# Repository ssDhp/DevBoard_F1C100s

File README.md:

# DevBoard_F1C100s Rev 1
F1C100s based embedded Linux development board

## Schematic

## Layout
2 Layers 75x50 mm  

## Render

## Assembled PCB

## Note
- Board enumerates over USB but randomly resets likely due to missing bulk capacitor on VBUS.
- Other issues:
    - Wrong voltage on UVCC pin of F1C100s
    - Missing pull-up on CS pin of Flash

# DevBoard_F1C100s Rev2

## Schematic

## Layout
4 Layers 60x45mm

## Render

## Note
 - **TODO:** Assemble and Test rev 2 of the dev board.

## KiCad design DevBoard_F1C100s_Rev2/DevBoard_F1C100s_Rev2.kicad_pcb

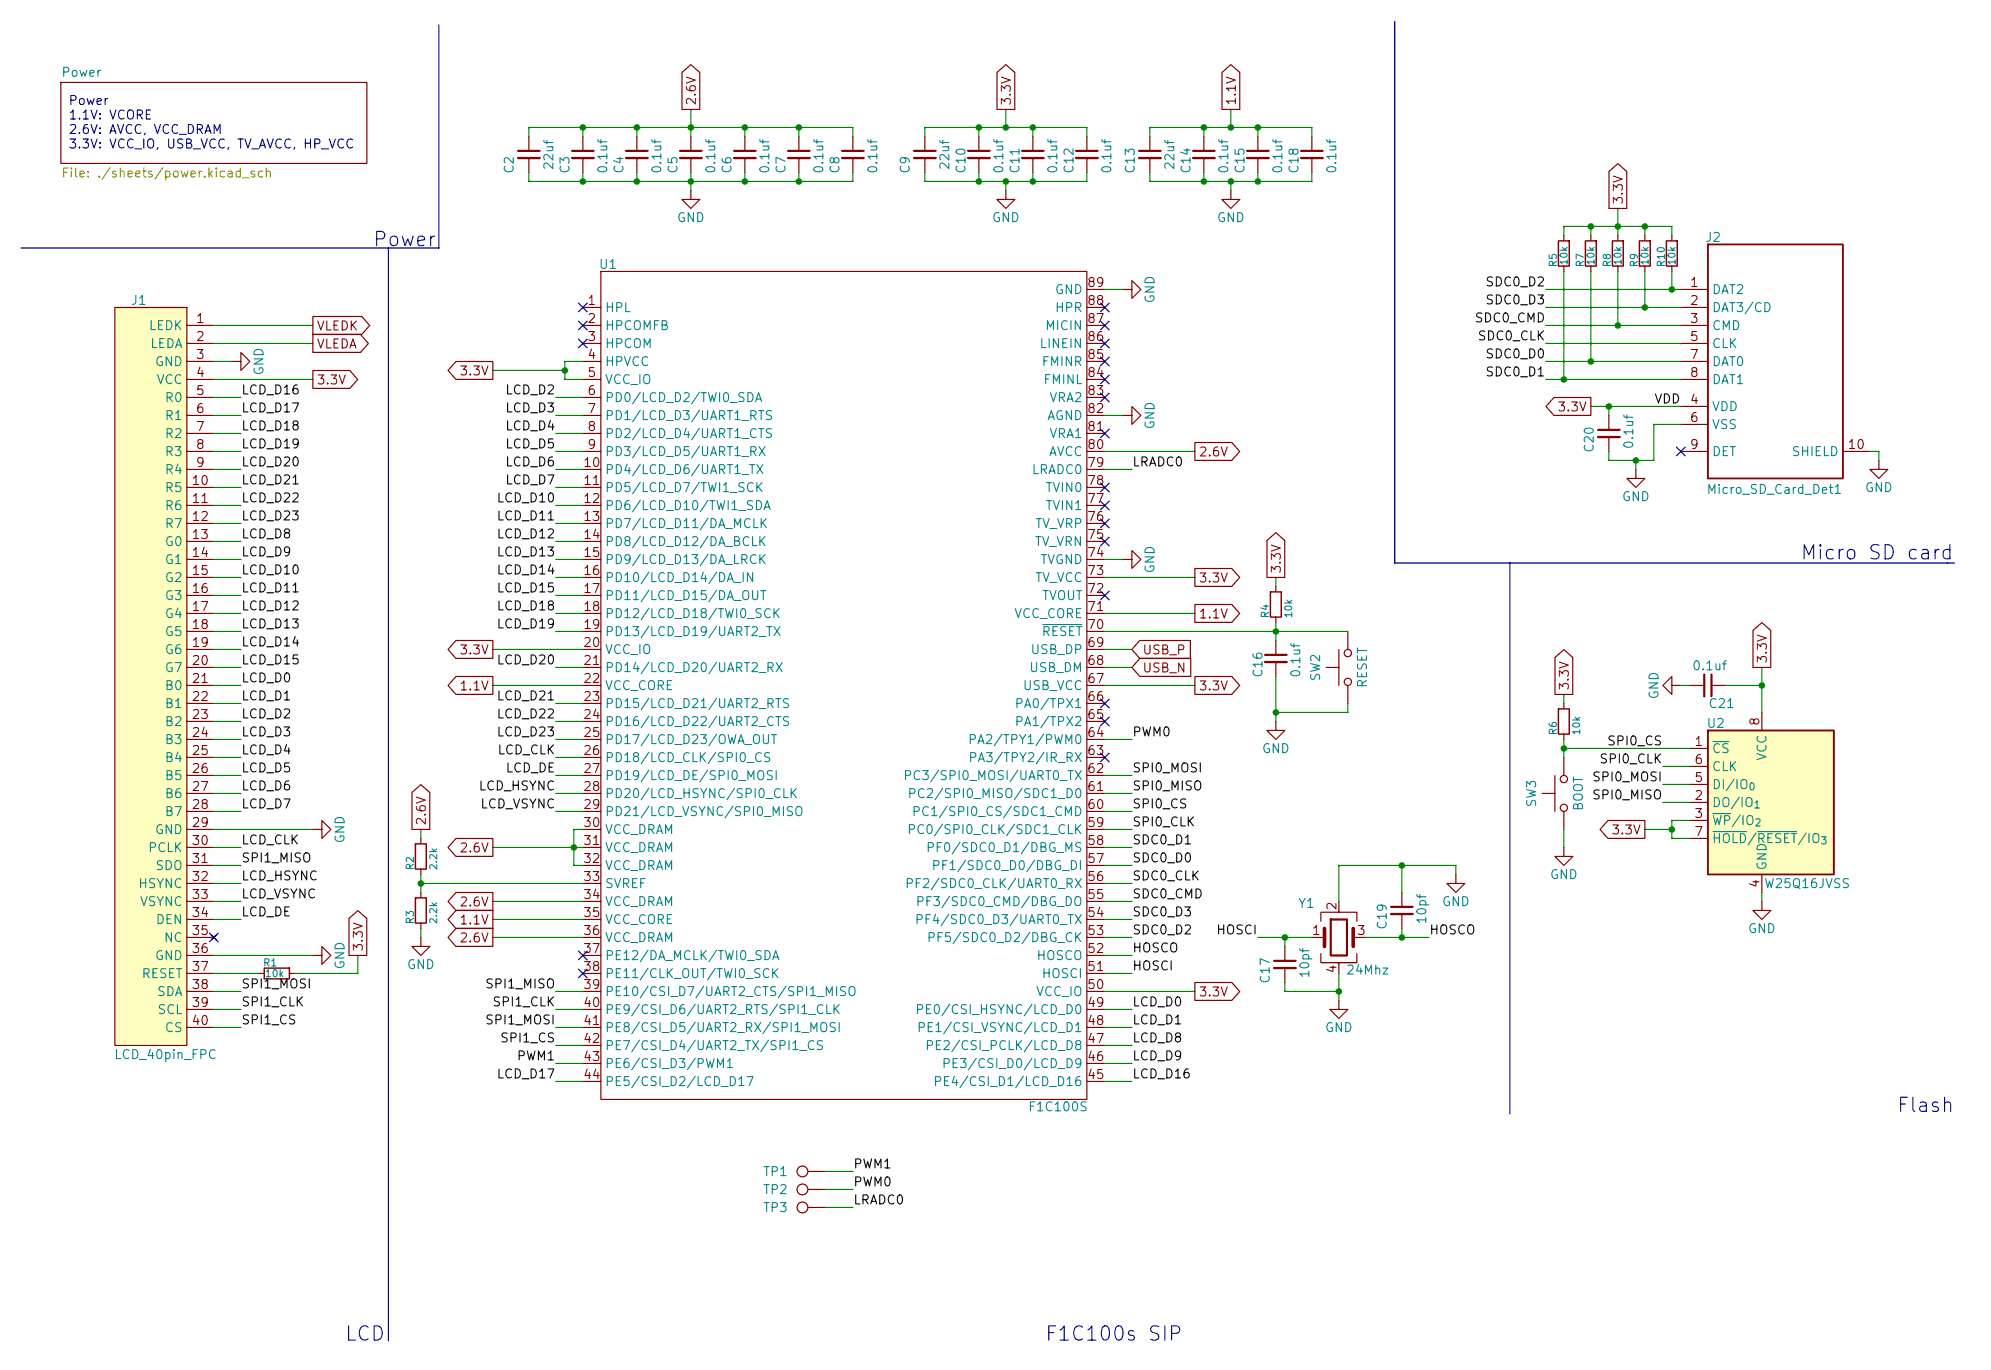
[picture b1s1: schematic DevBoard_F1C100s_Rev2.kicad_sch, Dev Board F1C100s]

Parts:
C2, C9, C13: 22uf; C_0603_1608Metric_Pad1.08x0.95mm_HandSolder
C3, C4, C5, C6, C7, C8, C10, C11, C12, C14, C15, C16, C18, C20, C21: 0.1uf; C_0603_1608Metric_Pad1.08x0.95mm_HandSolder
C17, C19: 10pf; C_0603_1608Metric_Pad1.08x0.95mm_HandSolder
J1: LCD_40pin_FPC; 40pin_0.5mm_Vertical
J2: Micro_SD_Card_Det1; sd_card_10p
R1, R4, R5, R6, R7, R8, R9, R10: 10k; R_0603_1608Metric_Pad0.98x0.95mm_HandSolder
R2, R3: 2.2k; R_0603_1608Metric_Pad0.98x0.95mm_HandSolder
SW2: RESET; SW_SPST_CK_RS282G05A3
SW3: BOOT; SW_SPST_CK_RS282G05A3
TP1, TP2, TP3: TestPoint; TestPoint_Pad_D1.0mm
U1: F1C100S; QFN-88_EP_10x10_Pitch0.4mm
U2: W25Q16JVSS; SOIC-8_5.3x5.3mm_P1.27mm
Y1: 24Mhz; Crystal_SMD_3225-4Pin_3.2x2.5mm_HandSoldering

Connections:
1.1V: C13.1, C14.1, C15.1, C18.1, U1.22 (VCC_CORE), U1.35 (VCC_CORE), U1.71 (VCC_CORE); also elsewhere on the board
2.6V: C2.1, C3.1, C4.1, C5.1, C6.1, C7.1, C8.1, R2.1, U1.30 (VCC_DRAM), U1.31 (VCC_DRAM), U1.32 (VCC_DRAM), U1.34 (VCC_DRAM), U1.36 (VCC_DRAM), U1.80 (AVCC); also elsewhere on the board
3.3V: C9.1, C10.1, C11.1, C12.1, C20.1, C21.1, J1.4 (VCC), J2.4 (VDD), R1.1, R4.1, R5.1, R6.1, R7.1, R8.1, R9.1, R10.1, U1.4 (HPVCC), U1.5 (VCC_IO), U1.20 (VCC_IO), U1.50 (VCC_IO), U1.67 (USB_VCC), U1.73 (TV_VCC), U2.3 (~WP/IO_{2}), U2.7 (~HOLD/~RESET/IO_{3}), U2.8 (VCC); also elsewhere on the board
/HOSCI: C17.1, U1.51 (HOSCI), Y1.1
/HOSCO: C19.2, U1.52 (HOSCO), Y1.3
/LCD_CLK: J1.30 (PCLK), U1.26 (PD18/LCD_CLK/SPI0_CS)
/LCD_D0: J1.21 (B0), U1.49 (PE0/CSI_HSYNC/LCD_D0)
/LCD_D1: J1.22 (B1), U1.48 (PE1/CSI_VSYNC/LCD_D1)
/LCD_D2: J1.23 (B2), U1.6 (PD0/LCD_D2/TWI0_SDA)
/LCD_D3: J1.24 (B3), U1.7 (PD1/LCD_D3/UART1_RTS)
/LCD_D4: J1.25 (B4), U1.8 (PD2/LCD_D4/UART1_CTS)
/LCD_D5: J1.26 (B5), U1.9 (PD3/LCD_D5/UART1_RX)
/LCD_D6: J1.27 (B6), U1.10 (PD4/LCD_D6/UART1_TX)
/LCD_D7: J1.28 (B7), U1.11 (PD5/LCD_D7/TWI1_SCK)
/LCD_D8: J1.13 (G0), U1.47 (PE2/CSI_PCLK/LCD_D8)
/LCD_D9: J1.14 (G1), U1.46 (PE3/CSI_D0/LCD_D9)
/LCD_D10: J1.15 (G2), U1.12 (PD6/LCD_D10/TWI1_SDA)
/LCD_D11: J1.16 (G3), U1.13 (PD7/LCD_D11/DA_MCLK)
/LCD_D12: J1.17 (G4), U1.14 (PD8/LCD_D12/DA_BCLK)
/LCD_D13: J1.18 (G5), U1.15 (PD9/LCD_D13/DA_LRCK)
/LCD_D14: J1.19 (G6), U1.16 (PD10/LCD_D14/DA_IN)
/LCD_D15: J1.20 (G7), U1.17 (PD11/LCD_D15/DA_OUT)
/LCD_D16: J1.5 (R0), U1.45 (PE4/CSI_D1/LCD_D16)
/LCD_D17: J1.6 (R1), U1.44 (PE5/CSI_D2/LCD_D17)
/LCD_D18: J1.7 (R2), U1.18 (PD12/LCD_D18/TWI0_SCK)
/LCD_D19: J1.8 (R3), U1.19 (PD13/LCD_D19/UART2_TX)
/LCD_D20: J1.9 (R4), U1.21 (PD14/LCD_D20/UART2_RX)
/LCD_D21: J1.10 (R5), U1.23 (PD15/LCD_D21/UART2_RTS)
/LCD_D22: J1.11 (R6), U1.24 (PD16/LCD_D22/UART2_CTS)
/LCD_D23: J1.12 (R7), U1.25 (PD17/LCD_D23/OWA_OUT)
/LCD_DE: J1.34 (DEN), U1.27 (PD19/LCD_DE/SPI0_MOSI)
/LCD_HSYNC: J1.32 (HSYNC), U1.28 (PD20/LCD_HSYNC/SPI0_CLK)
/LCD_VSYNC: J1.33 (VSYNC), U1.29 (PD21/LCD_VSYNC/SPI0_MISO)
/LRADC0: TP3.1, U1.79 (LRADC0)
/PWM0: TP2.1, U1.64 (PA2/TPY1/PWM0)
/PWM1: TP1.1, U1.43 (PE6/CSI_D3/PWM1)
/SDC0_CLK: J2.5 (CLK), U1.56 (PF2/SDC0_CLK/UART0_RX)
/SDC0_CMD: J2.3 (CMD), R8.2, U1.55 (PF3/SDC0_CMD/DBG_DO)
/SDC0_D0: J2.7 (DAT0), R7.2, U1.57 (PF1/SDC0_D0/DBG_DI)
/SDC0_D1: J2.8 (DAT1), R5.2, U1.58 (PF0/SDC0_D1/DBG_MS)
/SDC0_D2: J2.1 (DAT2), R10.2, U1.53 (PF5/SDC0_D2/DBG_CK)
/SDC0_D3: J2.2 (DAT3/CD), R9.2, U1.54 (PF4/SDC0_D3/UART0_TX)
/SPI0_CLK: U1.59 (PC0/SPI0_CLK/SDC1_CLK), U2.6 (CLK)
/SPI0_CS: R6.2, SW3.2, U1.60 (PC1/SPI0_CS/SDC1_CMD), U2.1 (~CS)
/SPI0_MISO: U1.61 (PC2/SPI0_MISO/SDC1_D0), U2.2 (DO/IO_{1})
/SPI0_MOSI: U1.62 (PC3/SPI0_MOSI/UART0_TX), U2.5 (DI/IO_{0})
/SPI1_CLK: J1.39 (SCL), U1.40 (PE9/CSI_D6/UART2_RTS/SPI1_CLK)
/SPI1_CS: J1.40 (CS), U1.42 (PE7/CSI_D4/UART2_TX/SPI1_CS)
/SPI1_MISO: J1.31 (SDO), U1.39 (PE10/CSI_D7/UART2_CTS/SPI1_MISO)
/SPI1_MOSI: J1.38 (SDA), U1.41 (PE8/CSI_D5/UART2_RX/SPI1_MOSI)
GND: C2.2, C3.2, C4.2, C5.2, C6.2, C7.2, C8.2, C9.2, C10.2, C11.2, C12.2, C13.2, C14.2, C15.2, C16.2, C17.2, C18.2, C19.1, C20.2, C21.2, J1.3 (GND), J1.29 (GND), J1.36 (GND), J2.6 (VSS), J2.10 (SHIELD), R3.2, SW2.1, SW3.1, U1.74 (TVGND), U1.82 (AGND), U1.89 (GND), U2.4 (GND), Y1.2, Y1.4; also elsewhere on the board
unnamed: J1.37 (RESET), R1.2
unnamed: R2.2, R3.1, U1.33 (SVREF)
unnamed: C16.1, R4.2, SW2.2, U1.70 (~RESET)
USB_N: U1.68 (USB_DM); also elsewhere on the board
USB_P: U1.69 (USB_DP); also elsewhere on the board
VLEDA: J1.2 (LEDA); also elsewhere on the board
VLEDK: J1.1 (LEDK); also elsewhere on the board

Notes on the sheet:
Micro SD card
LCD
Power
Flash
F1C100s SIP
Power 1.1V: VCORE 2.6V: AVCC, VCC_DRAM 3.3V: VCC_IO, USB_VCC, TV_AVCC, HP_VCC

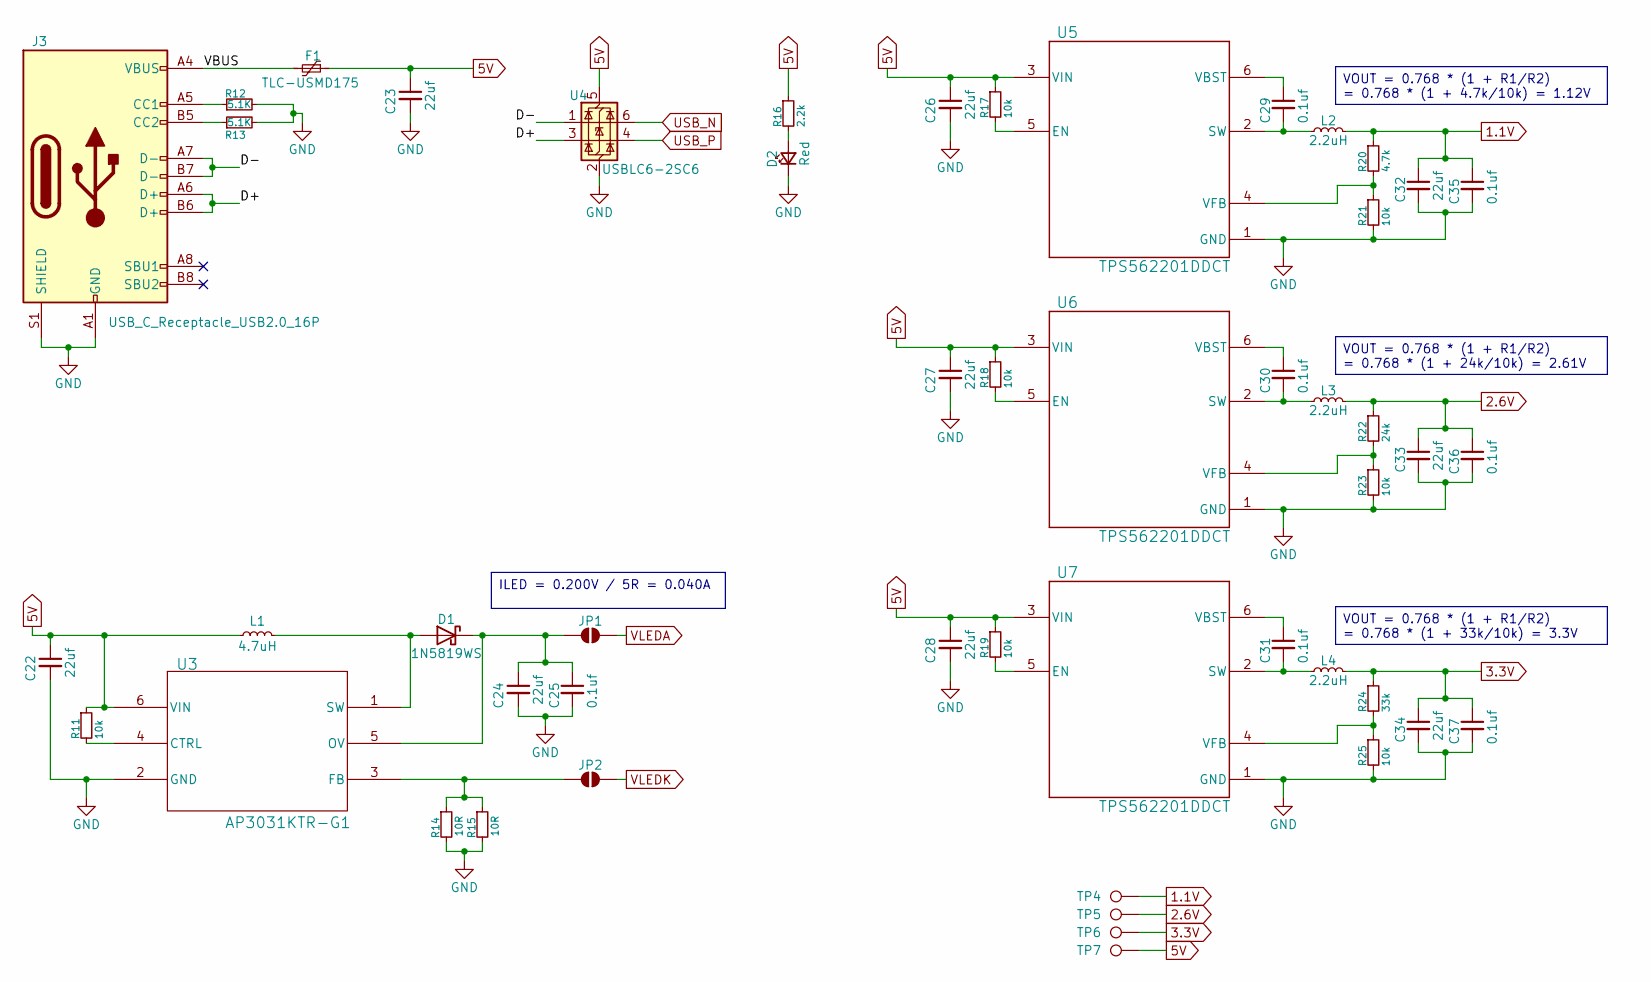
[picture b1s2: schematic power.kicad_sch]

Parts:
C22, C23, C24, C26, C27, C28, C32, C33, C34: 22uf; C_0603_1608Metric_Pad1.08x0.95mm_HandSolder
C25, C29, C30, C31, C35, C36, C37: 0.1uf; C_0603_1608Metric_Pad1.08x0.95mm_HandSolder
D1: 1N5819WS; D_SOD-523
D2: Red; LED_0603_1608Metric_Pad1.05x0.95mm_HandSolder
F1: TLC-USMD175; Fuse_1210_3225Metric_Pad1.42x2.65mm_HandSolder
J3: USB_C_Receptacle_USB2.0_16P; USB_C_Receptacle_HRO_TYPE-C-31-M-12
JP1, JP2: SolderJumper_2_Open; SolderJumper-2_P1.3mm_Open_Pad1.0x1.5mm
L1: 4.7uH; L_0805_2012Metric_Pad1.15x1.40mm_HandSolder
L2, L3, L4: 2.2uH; L_Sunlord_SWPA4030S
R11, R17, R18, R19, R21, R23, R25: 10k; R_0603_1608Metric_Pad0.98x0.95mm_HandSolder
R12, R13: 5.1K; R_0603_1608Metric_Pad0.98x0.95mm_HandSolder
R14, R15: 10R; R_0603_1608Metric_Pad0.98x0.95mm_HandSolder
R16: 2.2k; R_0603_1608Metric_Pad0.98x0.95mm_HandSolder
R20: 4.7k; R_0603_1608Metric_Pad0.98x0.95mm_HandSolder
R22: 24k; R_0603_1608Metric_Pad0.98x0.95mm_HandSolder
R24: 33k; R_0603_1608Metric_Pad0.98x0.95mm_HandSolder
TP4, TP5, TP6, TP7: TestPoint; TestPoint_Pad_D1.0mm
U3: AP3031KTR-G1; SOT23-6_DIO
U4: USBLC6-2SC6; SOT-23-6
U5, U6, U7: TPS562201DDCT; DDC0006A_N

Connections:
1.1V: C32.1, C35.1, L2.2, R20.1, TP4.1; also elsewhere on the board
2.6V: C33.1, C36.1, L3.2, R22.1, TP5.1; also elsewhere on the board
3.3V: C34.1, C37.1, L4.2, R24.1, TP6.1; also elsewhere on the board
5V: C22.1, C23.1, C26.1, C27.1, C28.1, F1.1, L1.1, R11.1, R16.1, R17.1, R18.1, R19.1, TP7.1, U3.6 (VIN), U4.5 (VBUS), U5.3 (VIN), U6.3 (VIN), U7.3 (VIN)
/Power/D+: J3.A6 (D+), J3.B6 (D+), U4.3 (I/O2)
/Power/D-: J3.A7 (D-), J3.B7 (D-), U4.1 (I/O1)
/Power/VBUS: F1.2, J3.A4 (VBUS), J3.A9 (VBUS), J3.B4 (VBUS), J3.B9 (VBUS)
GND: C22.2, C23.2, C24.2, C25.2, C26.2, C27.2, C28.2, C32.2, C33.2, C34.2, C35.2, C36.2, C37.2, D2.1 (K), J3.A1 (GND), J3.A12 (GND), J3.B1 (GND), J3.B12 (GND), J3.S1 (SHIELD), R12.2, R13.2, R14.2, R15.2, R21.2, R23.2, R25.2, U3.2 (GND), U4.2 (GND), U5.1 (GND), U6.1 (GND), U7.1 (GND); also elsewhere on the board
unnamed: D1.2 (A), L1.2, U3.1 (SW)
unnamed: C24.1, C25.1, D1.1 (K), JP1.1 (A), U3.5 (OV)
unnamed: D2.2 (A), R16.2
unnamed: J3.A5 (CC1), R12.1
unnamed: J3.B5 (CC2), R13.1
unnamed: JP2.1 (A), R14.1, R15.1, U3.3 (FB)
unnamed: R11.2, U3.4 (CTRL)
unnamed: R17.2, U5.5 (EN)
unnamed: C29.2, L2.1, U5.2 (SW)
unnamed: C29.1, U5.6 (VBST)
unnamed: R20.2, R21.1, U5.4 (VFB)
unnamed: R18.2, U6.5 (EN)
unnamed: C30.2, L3.1, U6.2 (SW)
unnamed: C30.1, U6.6 (VBST)
unnamed: R22.2, R23.1, U6.4 (VFB)
unnamed: R19.2, U7.5 (EN)
unnamed: C31.2, L4.1, U7.2 (SW)
unnamed: C31.1, U7.6 (VBST)
unnamed: R24.2, R25.1, U7.4 (VFB)
USB_N: U4.6 (I/O1); also elsewhere on the board
USB_P: U4.4 (I/O2); also elsewhere on the board
VLEDA: JP1.2 (B); also elsewhere on the board
VLEDK: JP2.2 (B); also elsewhere on the board

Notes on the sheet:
ILED = 0.200V / 5R = 0.040A
VOUT = 0.768 * (1 + R1/R2) = 0.768 * (1 + 4.7k/10k) = 1.12V
VOUT = 0.768 * (1 + R1/R2) = 0.768 * (1 + 24k/10k) = 2.61V
VOUT = 0.768 * (1 + R1/R2) = 0.768 * (1 + 33k/10k) = 3.3V

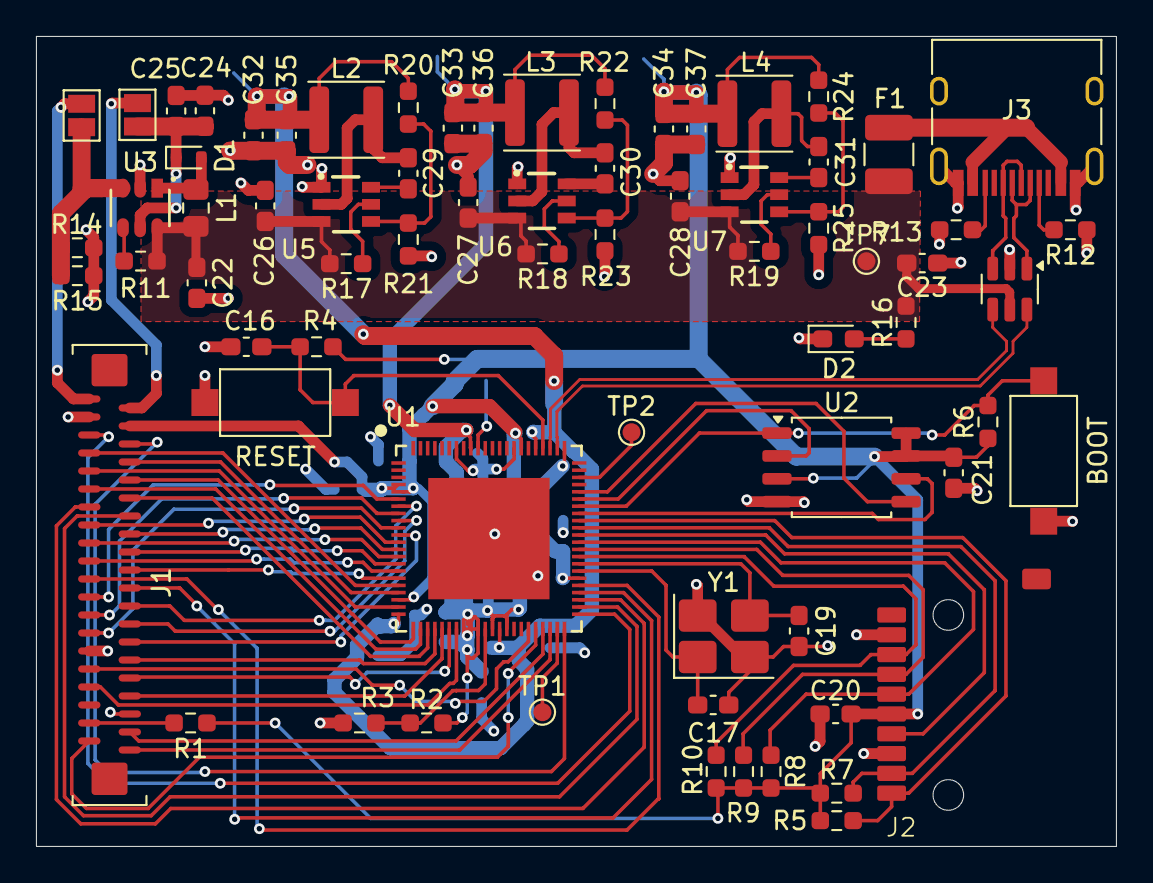
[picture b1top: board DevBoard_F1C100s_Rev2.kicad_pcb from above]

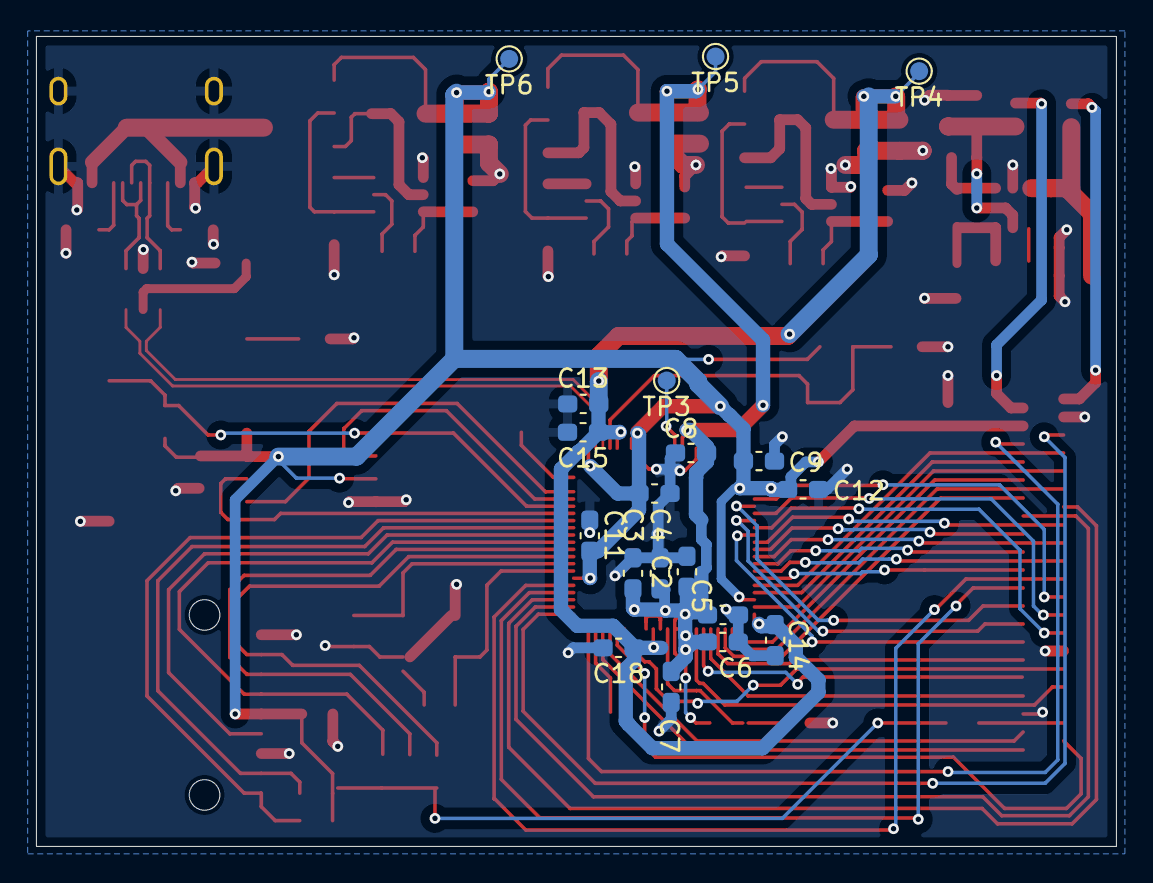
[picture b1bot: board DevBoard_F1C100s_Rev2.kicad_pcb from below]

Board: 4 copper layers, 60.0 x 45.0 mm, 90 parts (19 on the bottom side), 81 nets.

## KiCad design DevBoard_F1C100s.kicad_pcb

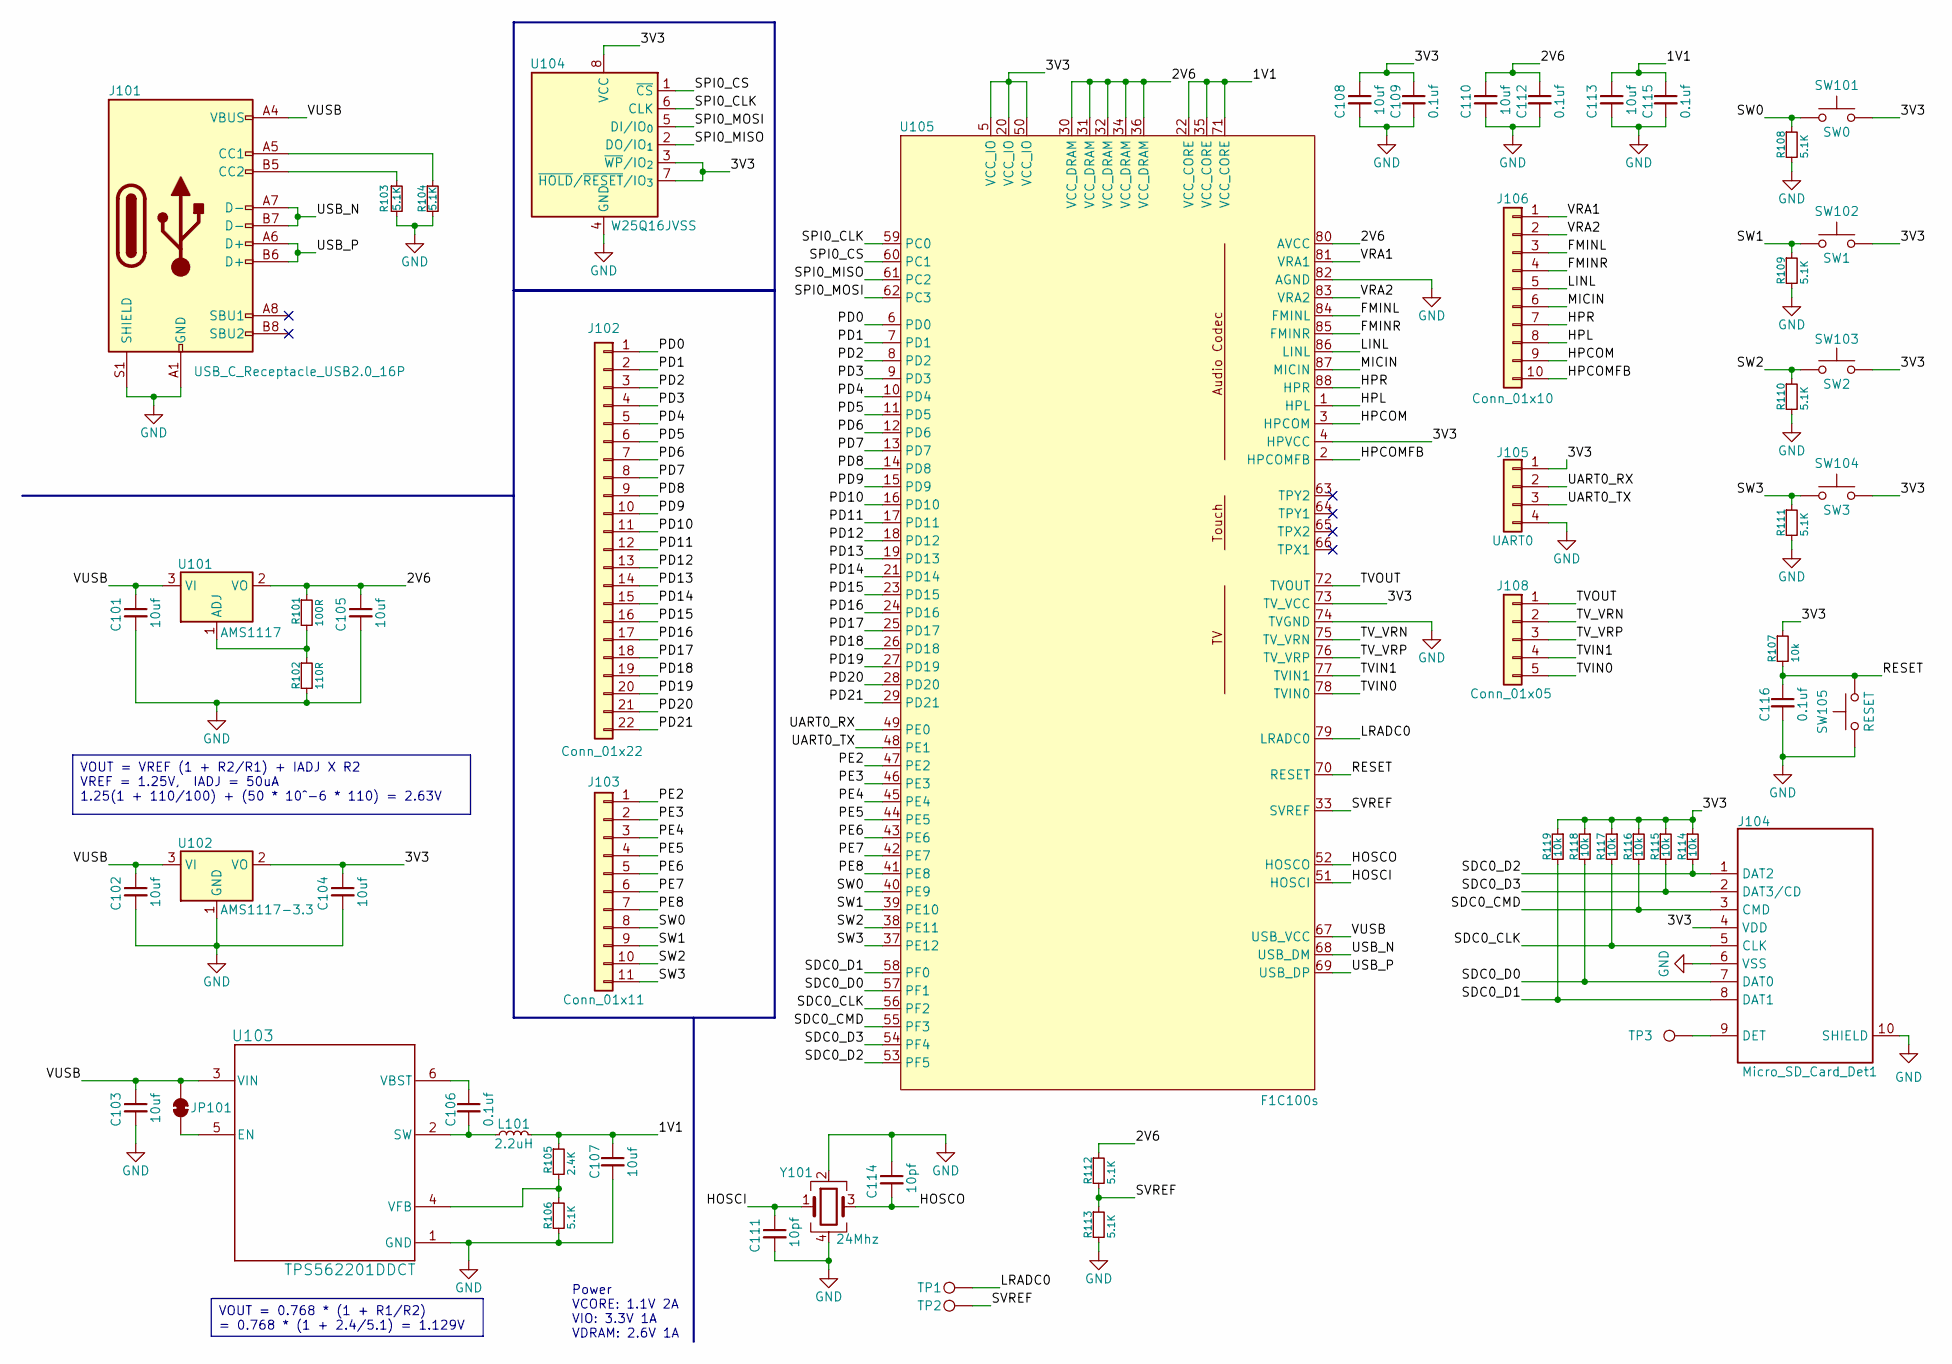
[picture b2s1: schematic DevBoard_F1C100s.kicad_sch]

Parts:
C101, C102, C103, C104, C105, C107, C108, C110, C113: 10uf; C_0603_1608Metric_Pad1.08x0.95mm_HandSolder
C106, C109, C112, C115, C116: 0.1uf; C_0603_1608Metric_Pad1.08x0.95mm_HandSolder
C111, C114: 10pf; C_0603_1608Metric_Pad1.08x0.95mm_HandSolder
J101: USB_C_Receptacle_USB2.0_16P; USB_C_Receptacle_Palconn_UTC16-G
J102: Conn_01x22; PinHeader_1x22_P1.00mm_Vertical_SMD_Pin1Left
J103: Conn_01x11; PinHeader_1x11_P1.00mm_Vertical_SMD_Pin1Left
J104: Micro_SD_Card_Det1; sd_card_10p
J105: UART0; PinHeader_1x04_P1.00mm_Vertical_SMD_Pin1Left
J106: Conn_01x10; PinHeader_1x10_P1.00mm_Vertical_SMD_Pin1Left
J108: Conn_01x05; PinHeader_1x05_P1.00mm_Vertical_SMD_Pin1Left
JP101: SolderJumper_2_Bridged; SolderJumper-2_P1.3mm_Bridged_RoundedPad1.0x1.5mm
L101: 2.2uH; L_APV_ANR252012
R101: 100R; R_0603_1608Metric_Pad0.98x0.95mm_HandSolder
R102: 110R; R_0603_1608Metric_Pad0.98x0.95mm_HandSolder
R103, R104, R106, R108, R109, R110, R111, R112, R113: 5.1K; R_0603_1608Metric_Pad0.98x0.95mm_HandSolder
R105: 2.4K; R_0603_1608Metric_Pad0.98x0.95mm_HandSolder
R107, R114, R115, R116, R117, R118, R119: 10k; R_0603_1608Metric_Pad0.98x0.95mm_HandSolder
SW101: SW0; SW_SPST_CK_RS282G05A3
SW102: SW1; SW_SPST_CK_RS282G05A3
SW103: SW2; SW_SPST_CK_RS282G05A3
SW104: SW3; SW_SPST_CK_RS282G05A3
SW105: RESET; SW_SPST_CK_RS282G05A3
TP1, TP2, TP3: TestPoint; TestPoint_Pad_D1.0mm
U101: AMS1117; SOT-223-3_TabPin2
U102: AMS1117-3.3; SOT-89-3_Handsoldering
U103: TPS562201DDCT; DDC0006A_N
U104: W25Q16JVSS; SOIC-8_5.3x5.3mm_P1.27mm
U105: F1C100s; QFN-88_EP_10x10_Pitch0.4mm
Y101: 24Mhz; Crystal_SMD_3225-4Pin_3.2x2.5mm_HandSoldering

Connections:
/1V1: C107.1, C113.1, C115.1, L101.2, R105.1, U105.22 (VCC_CORE), U105.35 (VCC_CORE), U105.71 (VCC_CORE)
/2V6: C105.1, C110.1, C112.1, R101.1, R112.1, U101.2 (VO), U105.30 (VCC_DRAM), U105.31 (VCC_DRAM), U105.32 (VCC_DRAM), U105.34 (VCC_DRAM), U105.36 (VCC_DRAM), U105.80 (AVCC)
/3V3: C104.1, C108.1, C109.1, J104.4 (VDD), J105.1, R107.1, R114.1, R115.1, R116.1, R117.1, R118.1, R119.1, SW101.2, SW102.2, SW103.2, SW104.2, U102.2 (VO), U104.3 (~WP/IO_{2}), U104.7 (~HOLD/~RESET/IO_{3}), U104.8 (VCC), U105.4 (HPVCC), U105.5 (VCC_IO), U105.20 (VCC_IO), U105.50 (VCC_IO), U105.73 (TV_VCC)
/FMINL: J106.3, U105.84 (FMINL)
/FMINR: J106.4, U105.85 (FMINR)
/HOSCI: C111.1, U105.51 (HOSCI), Y101.1
/HOSCO: C114.2, U105.52 (HOSCO), Y101.3
/HPCOM: J106.9, U105.3 (HPCOM)
/HPCOMFB: J106.10, U105.2 (HPCOMFB)
/HPL: J106.8, U105.1 (HPL)
/HPR: J106.7, U105.88 (HPR)
/LINL: J106.5, U105.86 (LINL)
/LRADC0: TP1.1, U105.79 (LRADC0)
/MICIN: J106.6, U105.87 (MICIN)
/PD0: J102.1, U105.6 (PD0)
/PD1: J102.2, U105.7 (PD1)
/PD2: J102.3, U105.8 (PD2)
/PD3: J102.4, U105.9 (PD3)
/PD4: J102.5, U105.10 (PD4)
/PD5: J102.6, U105.11 (PD5)
/PD6: J102.7, U105.12 (PD6)
/PD7: J102.8, U105.13 (PD7)
/PD8: J102.9, U105.14 (PD8)
/PD9: J102.10, U105.15 (PD9)
/PD10: J102.11, U105.16 (PD10)
/PD11: J102.12, U105.17 (PD11)
/PD12: J102.13, U105.18 (PD12)
/PD13: J102.14, U105.19 (PD13)
/PD14: J102.15, U105.21 (PD14)
/PD15: J102.16, U105.23 (PD15)
/PD16: J102.17, U105.24 (PD16)
/PD17: J102.18, U105.25 (PD17)
/PD18: J102.19, U105.26 (PD18)
/PD19: J102.20, U105.27 (PD19)
/PD20: J102.21, U105.28 (PD20)
/PD21: J102.22, U105.29 (PD21)
/PE2: J103.1, U105.47 (PE2)
/PE3: J103.2, U105.46 (PE3)
/PE4: J103.3, U105.45 (PE4)
/PE5: J103.4, U105.44 (PE5)
/PE6: J103.5, U105.43 (PE6)
/PE7: J103.6, U105.42 (PE7)
/PE8: J103.7, U105.41 (PE8)
/RESET: C116.1, R107.2, SW105.2, U105.70 (RESET)
/SDC0_CLK: J104.5 (CLK), R117.2, U105.56 (PF2)
/SDC0_CMD: J104.3 (CMD), R116.2, U105.55 (PF3)
/SDC0_D0: J104.7 (DAT0), R118.2, U105.57 (PF1)
/SDC0_D1: J104.8 (DAT1), R119.2, U105.58 (PF0)
/SDC0_D2: J104.1 (DAT2), R114.2, U105.53 (PF5)
/SDC0_D3: J104.2 (DAT3/CD), R115.2, U105.54 (PF4)
/SPI0_CLK: U104.6 (CLK), U105.59 (PC0)
/SPI0_CS: U104.1 (~CS), U105.60 (PC1)
/SPI0_MISO: U104.2 (DO/IO_{1}), U105.61 (PC2)
/SPI0_MOSI: U104.5 (DI/IO_{0}), U105.62 (PC3)
/SVREF: R112.2, R113.1, TP2.1, U105.33 (SVREF)
/SW0: J103.8, R108.1, SW101.1, U105.40 (PE9)
/SW1: J103.9, R109.1, SW102.1, U105.39 (PE10)
/SW2: J103.10, R110.1, SW103.1, U105.38 (PE11)
/SW3: J103.11, R111.1, SW104.1, U105.37 (PE12)
/TVIN0: J108.5, U105.78 (TVIN0)
/TVIN1: J108.4, U105.77 (TVIN1)
/TVOUT: J108.1, U105.72 (TVOUT)
/TV_VRN: J108.2, U105.75 (TV_VRN)
/TV_VRP: J108.3, U105.76 (TV_VRP)
/UART0_RX: J105.2, U105.49 (PE0)
/UART0_TX: J105.3, U105.48 (PE1)
/USB_N: J101.A7 (D-), J101.B7 (D-), U105.68 (USB_DM)
/USB_P: J101.A6 (D+), J101.B6 (D+), U105.69 (USB_DP)
/VRA1: J106.1, U105.81 (VRA1)
/VRA2: J106.2, U105.83 (VRA2)
/VUSB: C101.1, C102.1, C103.1, J101.A4 (VBUS), J101.A9 (VBUS), J101.B4 (VBUS), J101.B9 (VBUS), JP101.2 (B), U101.3 (VI), U102.3 (VI), U103.3 (VIN), U105.67 (USB_VCC)
GND: C101.2, C102.2, C103.2, C104.2, C105.2, C107.2, C108.2, C109.2, C110.2, C111.2, C112.2, C113.2, C114.1, C115.2, C116.2, J101.A1 (GND), J101.A12 (GND), J101.B1 (GND), J101.B12 (GND), J101.S1 (SHIELD), J104.6 (VSS), J104.10 (SHIELD), J105.4, R102.2, R103.2, R104.2, R106.2, R108.2, R109.2, R110.2, R111.2, R113.2, SW105.1, U102.1 (GND), U103.1 (GND), U104.4 (GND), U105.74 (TVGND), U105.82 (AGND), Y101.2, Y101.4
unnamed: J101.A5 (CC1), R104.1
unnamed: J101.B5 (CC2), R103.1
unnamed: J104.9 (DET), TP3.1
unnamed: JP101.1 (A), U103.5 (EN)
unnamed: R101.2, R102.1, U101.1 (ADJ)
unnamed: C106.2, L101.1, U103.2 (SW)
unnamed: C106.1, U103.6 (VBST)
unnamed: R105.2, R106.1, U103.4 (VFB)

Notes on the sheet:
Power VCORE: 1.1V 2A VIO: 3.3V 1A VDRAM: 2.6V 1A
VOUT = VREF (1 + R2/R1) + IADJ X R2 VREF = 1.25V, IADJ = 50uA 1.25(1 + 110/100) + (50 * 10^-6 * 110) = 2.63V
VOUT = 0.768 * (1 + R1/R2) = 0.768 * (1 + 2.4/5.1) = 1.129V

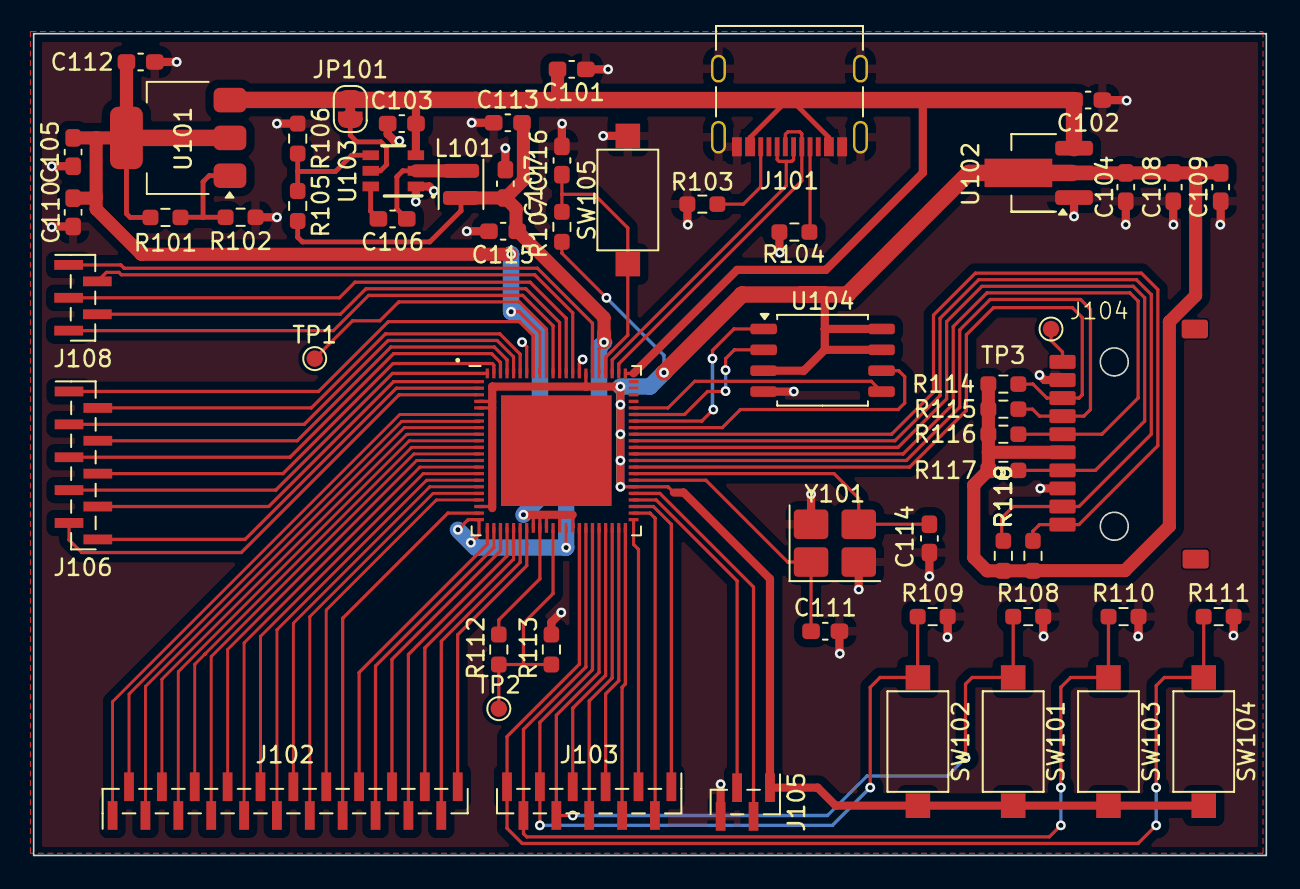
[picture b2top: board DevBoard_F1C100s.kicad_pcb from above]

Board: 2 copper layers, 75.0 x 50.0 mm, 58 parts (0 on the bottom side), 80 nets.

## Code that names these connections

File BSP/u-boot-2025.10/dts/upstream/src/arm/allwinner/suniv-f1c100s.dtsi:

// SPDX-License-Identifier: (GPL-2.0+ OR X11)
/*
 * Copyright 2018 Icenowy Zheng <icenowy@aosc.io>
 * Copyright 2018 Mesih Kilinc <mesihkilinc@gmail.com>
 */

#include <dt-bindings/clock/suniv-ccu-f1c100s.h>
#include <dt-bindings/reset/suniv-ccu-f1c100s.h>
#include <dt-bindings/dma/sun4i-a10.h>

/ {
	#address-cells = <1>;
	#size-cells = <1>;
	interrupt-parent = <&intc>;

	clocks {
		osc24M: clk-24M {
			#clock-cells = <0>;
			compatible = "fixed-clock";
			clock-frequency = <24000000>;
			clock-output-names = "osc24M";
		};

		osc32k: clk-32k {
			#clock-cells = <0>;
			compatible = "fixed-clock";
			clock-frequency = <32768>;
			clock-output-names = "osc32k";
		};
	};

	cpus {
		#address-cells = <1>;
		#size-cells = <0>;

		cpu@0 {
			compatible = "arm,arm926ej-s";
			device_type = "cpu";
			reg = <0x0>;
		};
	};

	soc {
		compatible = "simple-bus";
		#address-cells = <1>;
		#size-cells = <1>;
		ranges;

		sram-controller@1c00000 {
			compatible = "allwinner,suniv-f1c100s-system-control",
				     "allwinner,sun4i-a10-system-control";
			reg = <0x01c00000 0x30>;
			#address-cells = <1>;
			#size-cells = <1>;
			ranges;

			sram_d: sram@10000 {
				compatible = "mmio-sram";
				reg = <0x00010000 0x1000>;
				#address-cells = <1>;
				#size-cells = <1>;
				ranges = <0 0x00010000 0x1000>;

				otg_sram: sram-section@0 {
					compatible = "allwinner,suniv-f1c100s-sram-d",
						     "allwinner,sun4i-a10-sram-d";
					reg = <0x0000 0x1000>;
					status = "disabled";
				};
			};
		};

		spi0: spi@1c05000 {
			compatible = "allwinner,suniv-f1c100s-spi",
				     "allwinner,sun8i-h3-spi";
			reg = <0x01c05000 0x1000>;
			interrupts = <10>;
			clocks = <&ccu CLK_BUS_SPI0>, <&ccu CLK_BUS_SPI0>;
			clock-names = "ahb", "mod";
			resets = <&ccu RST_BUS_SPI0>;
			status = "disabled";
			num-cs = <1>;
			#address-cells = <1>;
			#size-cells = <0>;
		};

		spi1: spi@1c06000 {
			compatible = "allwinner,suniv-f1c100s-spi",
				     "allwinner,sun8i-h3-spi";
			reg = <0x01c06000 0x1000>;
			interrupts = <11>;
			clocks = <&ccu CLK_BUS_SPI1>, <&ccu CLK_BUS_SPI1>;
			clock-names = "ahb", "mod";
			resets = <&ccu RST_BUS_SPI1>;
			status = "disabled";
			num-cs = <1>;
			#address-cells = <1>;
			#size-cells = <0>;
		};

		mmc0: mmc@1c0f000 {
			compatible = "allwinner,suniv-f1c100s-mmc",
				     "allwinner,sun7i-a20-mmc";
			reg = <0x01c0f000 0x1000>;
			clocks = <&ccu CLK_BUS_MMC0>,
				 <&ccu CLK_MMC0>,
				 <&ccu CLK_MMC0_OUTPUT>,
				 <&ccu CLK_MMC0_SAMPLE>;
			clock-names = "ahb", "mmc", "output", "sample";
			resets = <&ccu RST_BUS_MMC0>;
			reset-names = "ahb";
			interrupts = <23>;
			pinctrl-names = "default";
			pinctrl-0 = <&mmc0_pins>;
			status = "disabled";
			#address-cells = <1>;
			#size-cells = <0>;
		};

		mmc1: mmc@1c10000 {
			compatible = "allwinner,suniv-f1c100s-mmc",
				     "allwinner,sun7i-a20-mmc";
			reg = <0x01c10000 0x1000>;
			clocks = <&ccu CLK_BUS_MMC1>,
				 <&ccu CLK_MMC1>,
				 <&ccu CLK_MMC1_OUTPUT>,
				 <&ccu CLK_MMC1_SAMPLE>;
			clock-names = "ahb", "mmc", "output", "sample";
			resets = <&ccu RST_BUS_MMC1>;
			reset-names = "ahb";
			interrupts = <24>;
			status = "disabled";
			#address-cells = <1>;
			#size-cells = <0>;
		};

		usb_otg: usb@1c13000 {
			compatible = "allwinner,suniv-f1c100s-musb";
			reg = <0x01c13000 0x0400>;
			clocks = <&ccu CLK_BUS_OTG>;
			resets = <&ccu RST_BUS_OTG>;
			interrupts = <26>;
			interrupt-names = "mc";
			phys = <&usbphy 0>;
			phy-names = "usb";
			extcon = <&usbphy 0>;
			allwinner,sram = <&otg_sram 1>;
			status = "disabled";
		};

		usbphy: phy@1c13400 {
			compatible = "allwinner,suniv-f1c100s-usb-phy";
			reg = <0x01c13400 0x10>;
			reg-names = "phy_ctrl";
			clocks = <&ccu CLK_USB_PHY0>;
			clock-names = "usb0_phy";
			resets = <&ccu RST_USB_PHY0>;
			reset-names = "usb0_reset";
			#phy-cells = <1>;
			status = "disabled";
		};

		dma: dma-controller@1c02000 {
			compatible = "allwinner,suniv-f1c100s-dma";
			reg = <0x01c02000 0x1000>;
			interrupts = <18>;
			clocks = <&ccu CLK_BUS_DMA>;
			resets = <&ccu RST_BUS_DMA>;
			#dma-cells = <2>;
		};

		ccu: clock@1c20000 {
			compatible = "allwinner,suniv-f1c100s-ccu";
			reg = <0x01c20000 0x400>;
			clocks = <&osc24M>, <&osc32k>;
			clock-names = "hosc", "losc";
			#clock-cells = <1>;
			#reset-cells = <1>;
		};

		intc: interrupt-controller@1c20400 {
			compatible = "allwinner,suniv-f1c100s-ic";
			reg = <0x01c20400 0x400>;
			interrupt-controller;
			#interrupt-cells = <1>;
		};

		pio: pinctrl@1c20800 {
			compatible = "allwinner,suniv-f1c100s-pinctrl";
			reg = <0x01c20800 0x400>;
			interrupts = <38>, <39>, <40>;
			clocks = <&ccu CLK_BUS_PIO>, <&osc24M>, <&osc32k>;
			clock-names = "apb", "hosc", "losc";
			gpio-controller;
			interrupt-controller;
			#interrupt-cells = <3>;
			#gpio-cells = <3>;

			mmc0_pins: mmc0-pins {
				pins = "PF0", "PF1", "PF2", "PF3", "PF4", "PF5";
				function = "mmc0";
				drive-strength = <30>;
			};

			/omit-if-no-ref/
			i2c0_pd_pins: i2c0-pd-pins {
				pins = "PD0", "PD12";
				function = "i2c0";
			};

			spi0_pc_pins: spi0-pc-pins {
				pins = "PC0", "PC1", "PC2", "PC3";
				function = "spi0";
			};

			uart0_pe_pins: uart0-pe-pins {
				pins = "PE0", "PE1";
				function = "uart0";
			};

			/omit-if-no-ref/
			uart1_pa_pins: uart1-pa-pins {
				pins = "PA2", "PA3";
				function = "uart1";
			};

			uart1_pd_pins: uart1-pd-pins {
				pins = "PD4", "PD3";
				function = "uart1";
			};
		};

		i2c0: i2c@1c27000 {
			compatible = "allwinner,suniv-f1c100s-i2c",
				     "allwinner,sun6i-a31-i2c";
			reg = <0x01c27000 0x400>;
			interrupts = <7>;
			clocks = <&ccu CLK_BUS_I2C0>;
			resets = <&ccu RST_BUS_I2C0>;
			#address-cells = <1>;
			#size-cells = <0>;
			status = "disabled";
		};

		i2c1: i2c@1c27400 {
			compatible = "allwinner,suniv-f1c100s-i2c",
				     "allwinner,sun6i-a31-i2c";
			reg = <0x01c27400 0x400>;
			interrupts = <8>;
			clocks = <&ccu CLK_BUS_I2C1>;
			resets = <&ccu RST_BUS_I2C1>;
			#address-cells = <1>;
			#size-cells = <0>;
			status = "disabled";
		};

		i2c2: i2c@1c27800 {
			compatible = "allwinner,suniv-f1c100s-i2c",
				     "allwinner,sun6i-a31-i2c";
			reg = <0x01c27800 0x400>;
			interrupts = <9>;
			clocks = <&ccu CLK_BUS_I2C2>;
			resets = <&ccu RST_BUS_I2C2>;
			#address-cells = <1>;
			#size-cells = <0>;
			status = "disabled";
		};

		timer@1c20c00 {
			compatible = "allwinner,suniv-f1c100s-timer";
			reg = <0x01c20c00 0x90>;
			interrupts = <13>, <14>, <15>;
			clocks = <&osc24M>;
		};

		wdt: watchdog@1c20ca0 {
			compatible = "allwinner,suniv-f1c100s-wdt",
				     "allwinner,sun6i-a31-wdt";
			reg = <0x01c20ca0 0x20>;
			interrupts = <16>;
			clocks = <&osc32k>;
		};

		pwm: pwm@1c21000 {
			compatible = "allwinner,suniv-f1c100s-pwm",
				     "allwinner,sun7i-a20-pwm";
			reg = <0x01c21000 0x400>;
			clocks = <&osc24M>;
			#pwm-cells = <3>;
			status = "disabled";
		};

		ir: ir@1c22c00 {
			compatible = "allwinner,suniv-f1c100s-ir",
				     "allwinner,sun6i-a31-ir";
			reg = <0x01c22c00 0x400>;
			clocks = <&ccu CLK_BUS_IR>, <&ccu CLK_IR>;
			clock-names = "apb", "ir";
			resets = <&ccu RST_BUS_IR>;
			interrupts = <6>;
			status = "disabled";
		};

		lradc: lradc@1c23400 {
			compatible = "allwinner,suniv-f1c100s-lradc",
				     "allwinner,sun8i-a83t-r-lradc";
			reg = <0x01c23400 0x400>;
			interrupts = <22>;
			status = "disabled";
		};

		uart0: serial@1c25000 {
			compatible = "snps,dw-apb-uart";
			reg = <0x01c25000 0x400>;
			interrupts = <1>;
			reg-shift = <2>;
			reg-io-width = <4>;
			clocks = <&ccu CLK_BUS_UART0>;
			resets = <&ccu RST_BUS_UART0>;
			status = "disabled";
		};

		uart1: serial@1c25400 {
			compatible = "snps,dw-apb-uart";
			reg = <0x01c25400 0x400>;
			interrupts = <2>;
			reg-shift = <2>;
			reg-io-width = <4>;
			clocks = <&ccu CLK_BUS_UART1>;
			resets = <&ccu RST_BUS_UART1>;
			status = "disabled";
		};

		uart2: serial@1c25800 {
			compatible = "snps,dw-apb-uart";
			reg = <0x01c25800 0x400>;
			interrupts = <3>;
			reg-shift = <2>;
			reg-io-width = <4>;
			clocks = <&ccu CLK_BUS_UART2>;
			resets = <&ccu RST_BUS_UART2>;
			status = "disabled";
		};

		codec: codec@1c23c00 {
			#sound-dai-cells = <0>;
			compatible = "allwinner,suniv-f1c100s-codec";
			reg = <0x01c23c00 0x400>;
			interrupts = <21>;
			clocks = <&ccu CLK_BUS_CODEC>, <&ccu CLK_CODEC>;
			clock-names = "apb", "codec";
			dmas = <&dma SUN4I_DMA_NORMAL 12>,
			       <&dma SUN4I_DMA_NORMAL 12>;
			dma-names = "rx", "tx";
			resets = <&ccu RST_BUS_CODEC>;
			status = "disabled";
		};
	};
};

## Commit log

2025-06-20 Layout: Complete power section
2025-06-22 Schematic: Finished
2025-06-22 Routing: WIP
2025-06-24 Layout: Almost complete
2025-06-25 Finish design
2025-06-25 Fix ground pour clearance
2025-07-12 Update docs
2025-07-13 Setup project for Rev2
    - Restructure project
    - Simplify the schematic
2025-07-14 Add refrences
2025-07-17 WIP schematic
2025-07-20 Update submodule
2025-07-20 Fix submodules
    - Fix submodule path for Rev 1 board
    - Rename KBL_LCD_RGB_FPC_socket to KBL_LCD_RGB_FPC
2025-07-21 Finish schematic rev2
2025-07-21 Update schematic annotations
2025-07-21 Update schematic and footprints
2025-07-23 Finish layout
2025-07-24 Cleanup
2025-07-24 Update submodule new commits
2025-09-18 Add new images
    - Update README.md
2025-10-13 Update iBOM
2025-10-19 Add BSP
2025-10-20 Uboot works!
